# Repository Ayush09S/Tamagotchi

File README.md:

# Overview
A small digital pet as a physical device remake! It features four buttons and a buzzer. It also has an OLED display and can be recharged! The coding is made so that it can show it's emotions based on how it's treated. Whether it's not played with, not given sleep, it'll react. Make sure to keep it entertained! It also can be powered off into deep sleep in case you are busy and need to temporarily turn it off.

## Context
It was created as an entry to contribute to the Fallout Hackathon in Shenzhen run by Hack Club! It was quite involved, requiring the research of components, importing the EasyEda JLCPCB library of components library into Kicad, and properly understanding how to make a schematic and routing a PCB. I really liked the idea of a small, hand-held device that you can carry with you, and the idea of a tamagotchi is pretty sweet! It can also be used with both smaller LiPo batteries and medium sized ones too! It took 40+ hours to complete. I was really glad the coding was not crazy complicated!

## Zine

# Specs
- 4 Push Buttons
- Latching Power Switch
- OLED screen

# How To Create
1. Create the PCB
  - Cut the PCB (with the Gerber file) through JLCPCB or a CNC machine and solder bought components needed (found in the BOM)
  - Use the provided files to solder header pins and components in the right places (Onshape link is a good one)

2. Print the models
  - Print the Casing, spacers and battery holder lid with the 3D Files provided on a 3D Printer (Note, the casing top, casing bottom, spacers and battery holder lid should all be printed seperately)
    OR
  - Buy the Casing printed from a printing service

3. Put it together
  - Put a bought or owned LiPo Battery and connect it to the bottom of the pcb, and place it into the allocated space in the casing
  - Use M3 Screws and nuts (buy or use owned ones) to screw the casing and PCB together

5. Program the PCB. (Sourced from [Tamagotchi Firmware Tutorial](https://fallout.hackclub.com/docs/guided-projects/tamagotchi-firmware#step-1-install-the-esp32-board-package))
  - Connect to the Tamagotchi's USB-C connector through a computer and apply the program provided through the Arduino IDE.
  - Make sure to downlooad to follow the steps below to get the correct libraries.
    
  - Open the Arduino IDE.
  - Go to File > Preferences (or Arduino IDE > Settings on macOS).
  - In the "Additional Boards Manager URLs" field, add the following URL: https://espressif.github.io/arduino-esp32/package_esp32_index.json > Note: If you already have URLs here, separate entries with commas.
  - Click OK to save the preferences.
  - Wait for the board index to download.

  - Open the Boards Manager by navigating to Tools > Board > Boards Manager.
  - In the search bar, type esp32.
  - Locate the entry for "esp32 by Espressif Systems".
  - Click the Install button. > Important: Ensure you are using version 3.0.0 or later, which supports the C6.
  - Wait for the installation to finish.

  - After installation, go to Tools > Board > esp32.
  - Select your board model: XIAO ESP32C6.

  - In Sketch > Include Library > Manage Libraries, install:
  -   Adafruit SSD1306 (by Adafruit)
  -   Adafruit GFX Library (by Adafruit), which will be prompted as a dependency.

  - Upload the code!

6. Done! Use the Tamagotchi as much as your heart desires!

# Full Design

# PCB
## Board

## Schematic

# Casing
Onshape Link (Do not click, copy and paste it): https://cad.onshape.com/documents/55ba759bd32af63245a8fd64/w/0539768004f2bf5a541f17f4/e/c03fca18856a8a03d68f317d?renderMode=0&uiState=6a38532017fe1dd1d0fb8e74
## Full

## Top

## Bottom

## Built

# BOM (AUD)
| No. | Item | Description | LCSC Supplier Number | Qty Req | Qty Must Buy | Unit Price | Total Price | Running Total | Link |
|:---|:---|:---|:---|:---|:---|:---|:---|:---|:---|
| 1 | 3D Print Filament | Elegoo PLA 1kg | | 1 | 1 | $19.95 | $19.95 | $19.95 | [Jaycar Link](https://www.jaycar.com.au/elegoo-pla-filament-brown-1-75mm-1kg/p/TL6415?srsltid=AfmBOorWonBfeYknAu3rB8aZ4PWmGkUiC_A2ZqcdQLrUnSMhugl3tplenB0) |
| | *Shipping* | Jaycar | | | | | $9.95 | $29.90 | |
| 2 | Screws | M3x30mm | | 4 | 10 | $0.13 | $1.33 | $31.23 | [Makerstore Link](https://www.makerstore.com.au/product/m3-button-head-screws-10-pack/?attribute_pa_length=30mm) |
| 3 | Nuts | M3 | | 4 | 4 | $0.14 | $0.56 | $31.79 | [Makerstore Link](https://www.makerstore.com.au/product/hard-m3nut-1/) |
| | *Shipping* | Makerstore | | | | | $7.50 | $39.29 | |
| 4 | Battery | LiPo Rechargeable 1100mAh | | 1 | 1 | $5.39 | $5.39 | $44.68 | [AliExpress Link](https://www.aliexpress.com/item/1005004824764461.html) |
| | *Shipping* | Aliexpress | | | | | $6.30 | $50.98 | |
| 5 | 7 Pin Headers | Male - 2.54mm Pitch | C6332200 | 2 | 20 | $0.04 | $0.72 | $51.70 | [LCSC Link](https://www.lcsc.com/product-detail/C6332200.html) |
| | 4 Pin Header | Male - 2.54mm Pitch | C5116483 | 1 | 20 | $0.03 | $0.64 | $52.34 | [LCSC Link](https://www.lcsc.com/product-detail/Pin-Headers_ZHOURI-2-54-1-4_C5116483.html) |
| 6 | Buzzer | BUZ-TH_BD12.5-P6.50-D1.4 | C49246964 | 1 | 10 | $0.08 | $0.82 | $53.16 | [LCSC Link](https://www.lcsc.com/product-detail/C49246964.html) |
| 7 | Push Buttons | SW-TH_4P-L4.5-W4.5-P3.00-LS4.8 | C2888493 | 4 | 50 | $0.02 | $0.75 | $53.91 | [LCSC Link](https://www.lcsc.com/product-image/C2888493.html) |
| 8 | Latching Button | SW-TH_TK-6580A-1 | C528770 | 1 | 1 | $0.31 | $0.31 | $54.22 | [LCSC Link](https://www.lcsc.com/product-detail/C528770.html) |
| 9 | OLED Screen | OLED-TH_L27.8-W27.2-P2.54_C9900033791 | C5248080 | 1 | 1 | $3.20 | $3.20 | $57.42 | [LCSC Link](https://www.lcsc.com/product-detail/C5248080.html) |
| | *Shipping* | LCSC | | | | | $9.10 | $66.52 | |
| | *Handling* | LCSC | | | | | $4.28 | $70.80 | |
| 10 | Microcontroller | XIAO-ESP32-C3-DIP-SMD | | 1 | 1 | $6.55 | $6.55 | $77.35 | [Seeed Studio Link](https://www.seeedstudio.com/Seeed-XIAO-ESP32C3-p-5431.html) |
| | *Shipping* | Seeed Studio | | | | | $7.05 | $84.40 | |
| 11 | PCB (without assembly) | Main board (Lead-Free Finish). Components to be soldered. | | 1 | 5 | $1.51 | $7.56 | $91.96 | [JLCPCB Link](https://jlcpcb.com/) |
| 11.2 | Additionals + Shipping | JLCPCB | | | | | $2.14 | $94.10 | |
| **-** | **Grand Total** | | | | | | | **$94.10** | |
# Additional Notes!
This was a Guided Project through Hack Club's Fallout's Docs. The github page of the tutorial is here https://github.com/TaniWanKenobi/tamagotchi. I really loved making it, and I really learnt a lot, just like with the USB Hub. If you are a beginner, I would suggest starting with a smaller project, but this project is INCREDIBLE as a second one! If you've got some experience programming, you'll definitely find this manageable to create.

WARNING - PRODUCTION FILES
The gerber is provided for the JLCPCB or any PCB cutting, but the BOM and CPL may not work properly when ordered, since the pins will not be assembled. This project is designed to have been soldered yourself, if you wish to alter it so that it can be ordered, you may do that but this project does not work in that way. YOU HAVE BEEN WARNED.

Sanity Checked by Kade Harrison and Revant Pandey

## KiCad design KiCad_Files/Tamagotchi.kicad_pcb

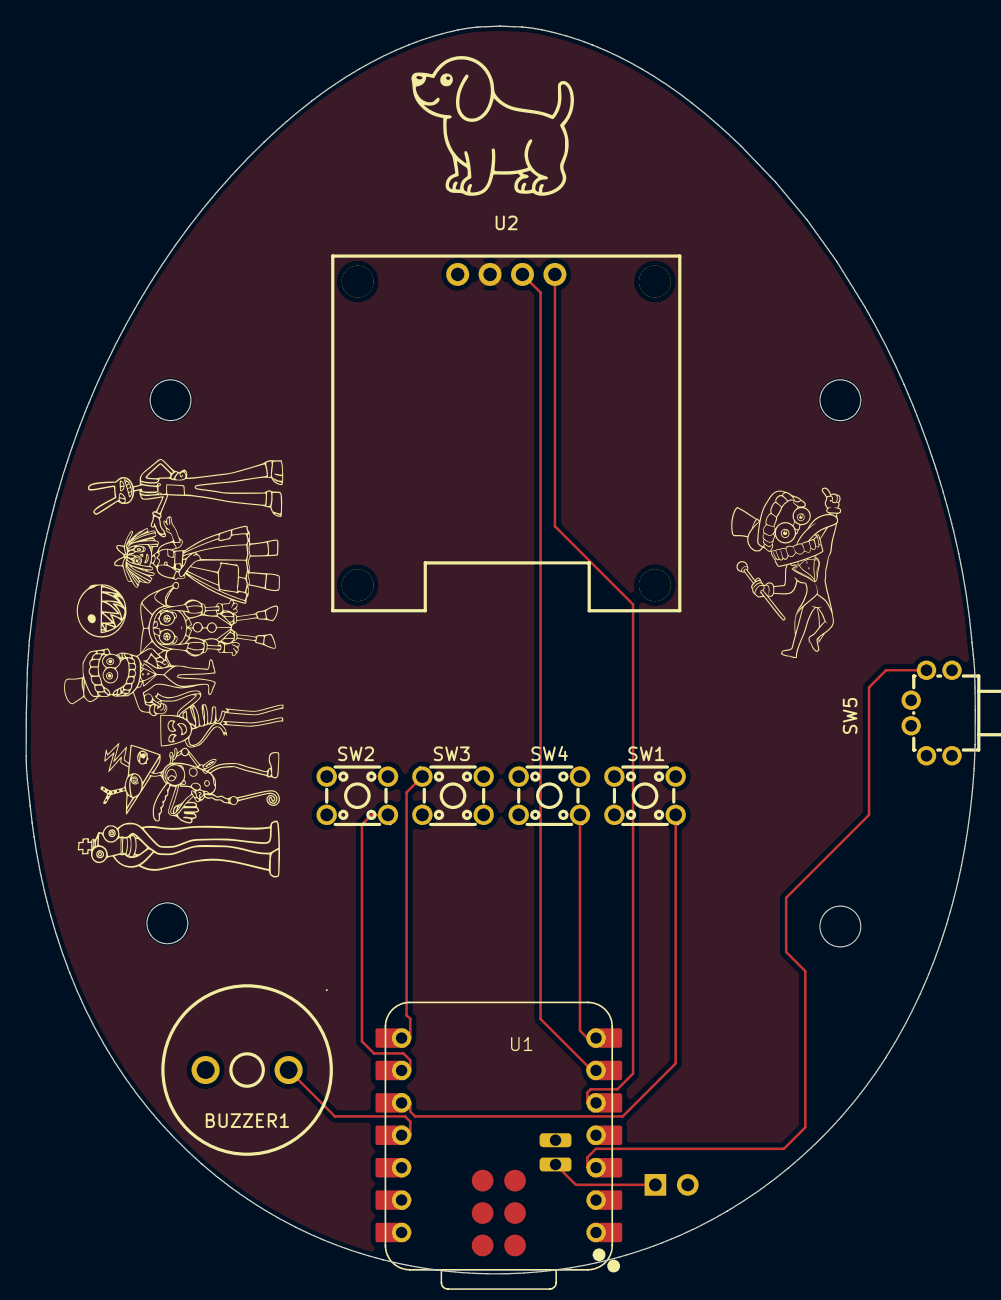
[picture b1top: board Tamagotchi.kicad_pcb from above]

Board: 2 copper layers, 74.4 x 97.8 mm, 9 parts (1 on the bottom side), 11 nets.

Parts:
BT1: Battery_Cell; PinHeader_1x02_P2.54mm_Vertical
BUZZER1: 1207-P6.5MM; BUZ-TH_BD12.5-P6.50-D1.4
SW1, SW2, SW3, SW4: TSC016A04518A; SW-TH_4P-L4.5-W4.5-P3.00-LS4.8
SW5: TK-6580A-1; SW-TH_TK-6580A-1
U1: XIAO-ESP32-C3-DIP-SMD
U2: HS96L03W2C03; OLED-TH_L27.8-W27.2-P2.54_C9900033791

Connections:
+3V3: U1.12 (3V3), U2.2 (VCC)
+BATT: BT1.1 (+), U1.22
GND: BT1.2 (-), BUZZER1.2 (-), SW1.4, SW2.4, SW3.4, SW4.4, SW5.3, U1.13 (GND), U1.21, U2.1 (GND)
unnamed: BUZZER1.1 (+), U1.11 (GPIO10_D10_MOSI)
unnamed: SW5.2, U1.3 (GPIO4_A2_D2)
unnamed: U1.5 (GPIO6_D4_SDA), U2.4 (SDA)
unnamed: U1.6 (GPIO7_D5_SCL), U2.3 (SCL)
unnamed: SW2.1, U1.9 (GPIO8_D8_SCK)
unnamed: SW1.1, U1.10 (GPIO9_D9_MISO)
unnamed: SW3.1, U1.8 (GPIO20_D7_RX)
unnamed: SW4.1, U1.7 (GPIO21_D6_TX)

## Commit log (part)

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2026-06-14 Add PCB images to README
    Added PCB images to the README for visual reference.
2026-06-14 Add temp.txt with initial content
2026-06-14 KiCad Source File import
2026-06-17 Update README with detailed creation instructions
    Expanded the README with detailed instructions on creating the Tamagotchi device, including PCB creation, casing, assembly, and programming.
2026-06-19 KiCad Source Files Upload
2026-06-19 Rename Tamagotchi.kicad_pcb to KiCad Files/Tamagotchi.kicad_pcb
2026-06-19 Rename Tamagotchi.kicad_pro to Kicad Files/Tamagotchi.kicad_pro
2026-06-19 Source files reuploaded
2026-06-19 Gerber Upload
2026-06-19 Rename Gerber.zip to Gerber/Gerber.zip
2026-06-19 Rename Tamagotchi-Battery_Lid.step to CAD/Tamagotchi-Battery_Lid.step
2026-06-19 Rename BOM-Tamagotchi.csv to Production Files/BOM-Tamagotchi.csv
2026-06-19 Fix grammar and formatting in README.md
    Corrected minor grammatical errors and formatting in the README.
2026-06-19 BOM Upload
2026-06-19 Rename Bill Of Materials.csv to BOM/Bill Of Materials.csv
2026-06-19 Add BOM section with item descriptions and links
    Added a Bill of Materials (BOM) section with item details.
2026-06-19 Add Onshape link to README
    Added Onshape link for casing reference.
2026-06-19 Zine Upload
2026-06-19 Rename Tamagotchi Zine.pdf to Zine/Tamagotchi Zine.pdf
2026-06-19 Zine Working Upload
2026-06-19 Rename Tamagotchi Zine (2).pdf to Tamagotchi Zine.pdf
2026-06-19 Upload again?..
2026-06-19 Add placeholder file with initial content for Zine
2026-06-19 Zine upload (now hopefully it'll work?)
2026-06-20 Create placeholder
2026-06-20 Firmware upload
2026-06-20 Add placeholder file in KiCad Files directory
2026-06-20 Create plasd
2026-06-20 Revise BOM formatting and section details
    Updated the BOM section and fixed formatting issues in the README.
2026-06-20 Add new PCB images to README
2026-06-20 Create asd
2026-06-20 Add new images to README sections
2026-06-20 Create ads
2026-06-20 Fix unit price and total for PCB in BOM
    Updated unit price for PCB and total price calculations.
2026-06-20 Create place
2026-06-20 Source File Upload
2026-06-20 Rename BOM-Tamagotchi.csv to BOM-Tamagotchi.csv
2026-06-20 Rename Tamagotchi.kicad_pcb to Tamagotchi.kicad_pcb
2026-06-20 updated one
2026-06-21 Update Onshape link instructions in README
2026-06-21 Rename CAD/Tamagotchi-Spacer_1_Part.step to CAD/Spacers/Tamagotchi-Spacer_1_Part.step
2026-06-21 Zine reupload
2026-06-21 Revise README with updated assembly instructions and BOM
    Updated instructions for PCB creation and assembly, clarified components needed, and revised BOM format with shipping costs.
2026-06-21 Create temp
2026-06-21 Fix completion time in README
    Updated the completion time from 35+ hours to 40+ hours in the context section.
2026-06-22 Revise README with additional project details
    Updated project notes with tutorial link and clarified warnings.
2026-06-22 Update README with design and PCB images
    Added design images and PCB details to the README.
2026-06-22 Replace Zine image link in README
    Updated the Zine section with a new image link.
    Easier QR Code to scan
2026-06-22 Better QR Code
